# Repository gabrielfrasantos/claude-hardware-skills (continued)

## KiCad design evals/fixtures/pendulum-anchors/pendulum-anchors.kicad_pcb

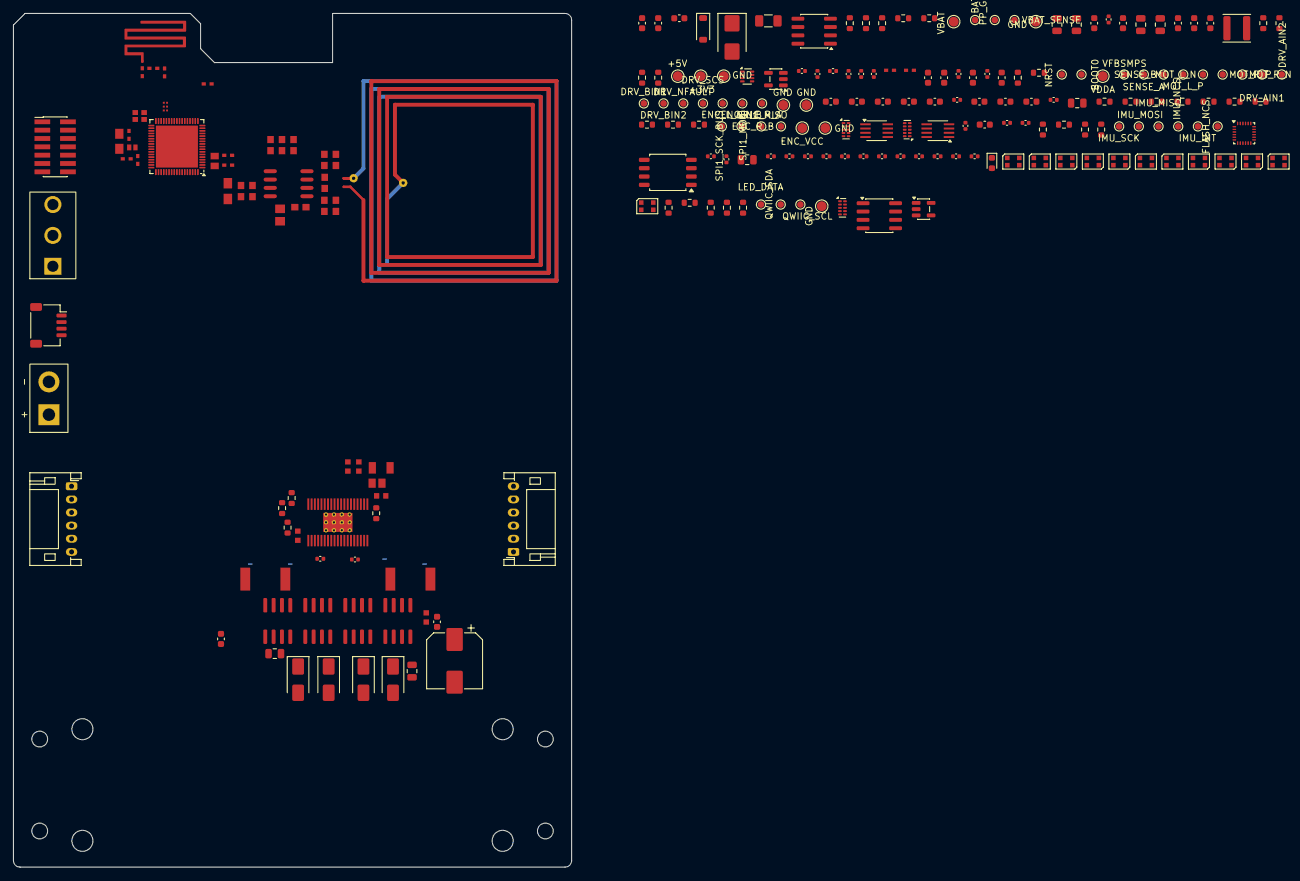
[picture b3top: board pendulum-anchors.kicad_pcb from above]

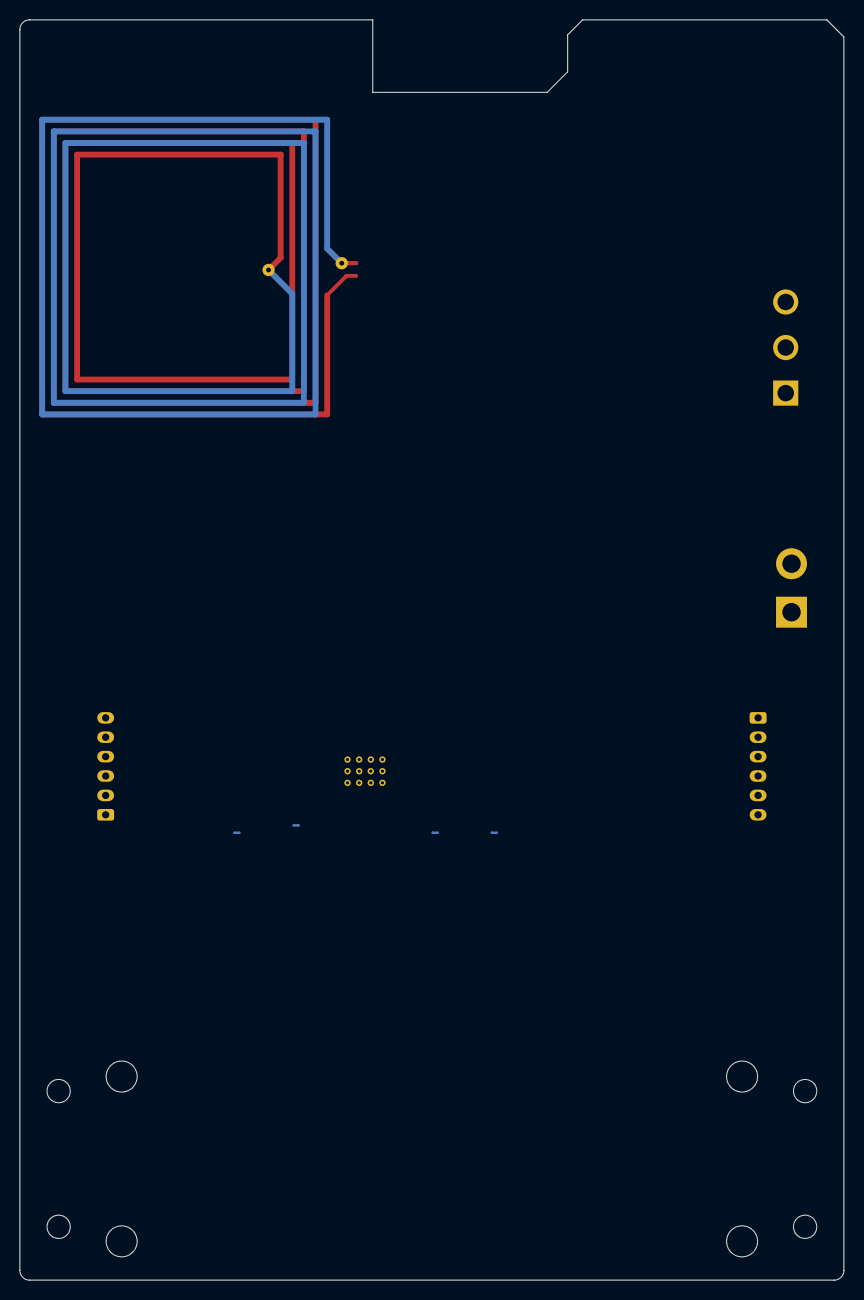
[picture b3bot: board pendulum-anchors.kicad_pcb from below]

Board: 4 copper layers, 85.0 x 130.0 mm, 245 parts (4 on the bottom side), 119 nets, no tracks yet.

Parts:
AE401: Meander antenna; MB1355_Meander_Antenna
AE801: ANT14; MB1163_ANT14
C101, C205: 47nF 50V; C_0603_1608Metric
C102, C209, C311, C313: 1uF 50V; C_0603_1608Metric
C103, C203, C208, C503, C506, C602, C603, C607: 100nF 50V; C_0603_1608Metric
C201, C202, C502, C505, C805: 10uF 25V; C_0805_2012Metric
C204, C301, C302, C303, C304, C305, C312, C317, C606, C610, C701, C703, C704, C801, C802, C806, C807, C808, C809, C810, C811, C812, C813, C814, C815, C816, C817: 100nF 16V; C_0402_1005Metric
C206, C207: 22uF 25V; C_0805_2012Metric
C210: 2.2uF 25V; C_0603_1608Metric
C306: 4.7uF 10V; C_0402_1005Metric
C307, C318: 100nF 16V; MB1355_0402_CAP_NPOL
C308: 100pF 50V; MB1355_0402_CAP_NPOL
C309, C314: 4.7uF 10V; MB1355_0402_CAP_NPOL
C310, C702: 10nF 50V; C_0603_1608Metric
C315, C316: 6.8pF 50V; MB1355_0402_CAP_NPOL
C401: NF; MB1355_0402_CAP_NPOL
C402: 1.2pF 50V; MB1355_0402_CAP_NPOL
C501, C504: 1nF 50V; C_0402_1005Metric
C507: 220u 35V; CP_Elec_8x10
C508: 10nF 100V; BOOST_0603L
C509: 1uF 50V; BOOST_0805L
C510: 100nF 100V; BOOST_0603L
C511: 100nF 25V; BOOST_0603L
C512: 1uF 16V; BOOST_0603L
C513: 1nF 16V; BOOST_0603L
C514: 1uF 100V; BOOST_1206L
C601: 10uF 10V; C_0603_1608Metric
C604, C605, C608, C609: 1nF 50V; C_0603_1608Metric
C803: 1uF 16V; MB1163_CP_293D_A
C804: 100nF 50V; MB1163_C_0603
C818: 100pF 50V; MB1163_C_0603
C819, C820: 47pF 50V; MB1163_C_0603
C821, C822, C823: NF; MB1163_C_0603
D101: BZT52C15; D_SOD-123
D102: SMBJ15A; D_SMB
D501, D502, D503, D504: SS34; D_SMA
D801: green; LED_0603_1608Metric
D802, D803, D804, D805, D806, D807, D808, D809, D810, D811, D812, D813: WS2812B-2020; LED_WS2812B-2020_PLCC4_2.0x2.0mm
F101: 4A fast; Fuse_1206_3216Metric
F601: PTC 100mA; Fuse_0805_2012Metric
FB301: BLM18PG221SN1D; L_0603_1608Metric
FB801: 742792042; MB1163_L_0805
FL401: MLPF-WB55-01E3; MB1355_ST_CSP650x58P2x3_160x100x42
J101: XT30 battery; AMASS_XT30UPB-F_1x02_P5.00mm_Vertical
J301: STDC14; PinHeader_2x07_P1.27mm_Vertical_SMD
J601: Motor left; JST_PH_S6B-PH-K_1x06_P2.00mm_Horizontal
J602: Motor right; JST_PH_S6B-PH-K_1x06_P2.00mm_Horizontal
J801: Qwiic; JST_SH_SM04B-SRSS-TB_1x04-1MP_P1.00mm_Horizontal
L201: 4.7uH; L_Sunlord_SWPA4030S
L301: 10uH; MB1355_0805_COIL
L302: 10nH; MB1355_IND_0402_MURATA_LQW15AN_H0P5
L401: 3.6nH; MB1355_0402_COIL
MB1, MB2, MB3, MB4: bracket M3; MountingHole_M3_NPTH_KeepOut7mm
MB5, MB6, MB7, MB8: bracket M2; MountingHole_M2_NPTH_KeepOut5.5mm
MC1, MC2, MC3, MC4: battery cradle; MountingHole_M3_NPTH_KeepOut7mm
MH1: bumper; MountingHole_M3_NPTH_KeepOut7mm
MH2: bumper (nylon); MountingHole_M3_NPTH_KeepOut7mm
NT501, NT502, NT503, NT504: NetTie; BOOST_Net-Tie_10mil
Q101: AO4805; SOIC-8_3.9x4.9mm_P1.27mm
Q501, Q502, Q503, Q504: CSD88537ND; BOOST_SO-8
R101, R102, R104: 100k; R_0603_1608Metric
R103: 1k; R_0603_1608Metric
R105: 27k; R_0603_1608Metric
R201: 240k; R_0603_1608Metric
R202: 36k; R_0603_1608Metric
R203: 52.3k; R_0603_1608Metric
R204, R302, R515, R516, R518, R701, R702, R703, R704, R803: 10k; R_0603_1608Metric
R301, R802: 33; R_0603_1608Metric
R401: 0; MB1355_0402_RES
R509, R512: 50m; BOOST_2512M
R517, R603, R605, R607, R609, R808, R809: 2.2k; R_0603_1608Metric
R601, R602: 0; R_0603_1608Metric
R604, R606, R608, R610: 100; R_0603_1608Metric
R801: 470; R_0603_1608Metric
R804: 30k; MB1163_R_0603
R805, R806: 4.7k; MB1163_R_0603
R810: 20k; MB1163_R_0603
SW101: SS-12D10L5; SW_Slide_SPDT_SS-12D10L5_P4.70mm
TP101: VBAT; TestPoint_Pad_D1.5mm
TP102: BAT_F; TestPoint_Pad_D1.0mm
TP103: PP_G; TestPoint_Pad_D1.0mm
TP104: VBAT_SENSE; TestPoint_Pad_D1.0mm
TP105, TP203, TP516, TP517, TP606, TP804: GND; TestPoint_Pad_D1.5mm
TP201: +5V; TestPoint_Pad_D1.5mm
TP202: +3V3; TestPoint_Pad_D1.5mm
TP301: NRST; TestPoint_Pad_D1.0mm
TP302: BOOT0; TestPoint_Pad_D1.0mm
TP303: VDDA; TestPoint_Pad_D1.5mm
TP304: VFBSMPS; TestPoint_Pad_D1.0mm
TP501: SENSE_A; TestPoint_Pad_D1.0mm
TP502: SENSE_B; TestPoint_Pad_D1.0mm
TP503: MOT_L_P; TestPoint_Pad_D1.0mm
TP504: MOT_L_N; TestPoint_Pad_D1.0mm
TP505: MOT_R_P; TestPoint_Pad_D1.0mm
TP506: MOT_R_N; TestPoint_Pad_D1.0mm
TP507: DRV_AIN1; TestPoint_Pad_D1.0mm
TP508: DRV_AIN2; TestPoint_Pad_D1.0mm
TP509: DRV_BIN1; TestPoint_Pad_D1.0mm
TP510: DRV_BIN2; TestPoint_Pad_D1.0mm
TP511: DRV_NFAULT; TestPoint_Pad_D1.0mm
TP512: DRV_SCS; TestPoint_Pad_D1.0mm
TP513: SPI1_SCK_BUS; TestPoint_Pad_D1.0mm
TP514: SPI1_MOSI; TestPoint_Pad_D1.0mm
TP515: SPI1_MISO; TestPoint_Pad_D1.0mm
TP601: ENC_L_A; TestPoint_Pad_D1.0mm
TP602: ENC_L_B; TestPoint_Pad_D1.0mm
TP603: ENC_R_A; TestPoint_Pad_D1.0mm
TP604: ENC_R_B; TestPoint_Pad_D1.0mm
TP605: ENC_VCC; TestPoint_Pad_D1.5mm
TP701: IMU_SCK; TestPoint_Pad_D1.0mm
TP702: IMU_MOSI; TestPoint_Pad_D1.0mm
TP703: IMU_MISO; TestPoint_Pad_D1.0mm
TP704: IMU_NCS; TestPoint_Pad_D1.0mm
TP705: IMU_INT; TestPoint_Pad_D1.0mm
TP706: FLASH_NCS; TestPoint_Pad_D1.0mm
TP801: LED_DATA; TestPoint_Pad_D1.0mm
TP802: QWIIC_SDA; TestPoint_Pad_D1.0mm
TP803: QWIIC_SCL; TestPoint_Pad_D1.0mm
U201: TPS62933F; SOT-583-8
U202: TLV75533P; SOT-23-5
U301: STM32WB55RGV6; QFN-68-1EP_8x8mm_P0.4mm_EP6.4x6.4mm
U501: DRV8711; BOOST_R-PDSO-G38
U601, U603, U801: TPD4E05U06QDQARQ1; USON-10_2.5x1.0mm_P0.5mm
U602, U604: SN74LVC3G17DCTR; SSOP-8_2.95x2.8mm_P0.65mm
U701: MPU-6500; InvenSense_QFN-24_3x3mm_P0.4mm
U702: W25Q16JVSSIQ; SOIC-8_5.3x5.3mm_P1.27mm
U802: M24C64-RMN6TP; SOIC-8_3.9x4.9mm_P1.27mm
U803: M24SR64-YMN6T/2; MB1163_SO8
U804: SN74AHCT1G125; SOT-23-5
Y301: 32MHz; MB1355_NX2016_4P
Y302: 32.768kHz; MB1355_NX2012_2P

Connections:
+3V3: C210.1, C301.1, C302.1, C303.1, C304.1, C305.1, C306.1, C307.1, C308.1, C309.1, C318.1, C606.1, C610.1, C701.1, C702.1, C704.1, C802.1, FB301.1, FB801.1, J301.3, J801.2, R515.2, R516.2, R517.2, R602.1, R701.2, R702.2, R703.2, R704.2, R805.2, R806.2, R808.2, R809.2, R810.2, TP202.1, U202.5, U301.1, U301.30, U301.33, U301.44, U301.45, U301.55, U301.68, U602.8, U604.8, U701.8, U701.13, U702.8, U801.4, U802.8
+5V: C206.1, C207.1, C208.1, C209.1, C801.1, C805.1, C806.1, C807.1, C808.1, C809.1, C810.1, C811.1, C812.1, C813.1, C814.1, C815.1, C816.1, C817.1, D802.4, D803.4, D804.4, D805.4, D806.4, D807.4, D808.4, D809.4, D810.4, D811.4, D812.4, D813.4, L201.2, R203.1, R601.1, TP201.1, U202.1, U202.3, U804.5
/1 Battery input and protection/BAT_F: F101.2, Q101.7, Q101.8, TP102.1
/1 Battery input and protection/BAT_P: F101.1, J101.1
/1 Battery input and protection/PP_G: C102.1, D101.2, Q101.2, Q101.4, R101.1, R102.1, R103.1, TP103.1
/1 Battery input and protection/PP_S: C102.2, D101.1, Q101.1, Q101.3, R101.2
/1 Battery input and protection/PP_SS: C101.1, R103.2
/1 Battery input and protection/SW_ON: R102.2, SW101.2
/2 5V0 buck and 3V3 LDO/BUCK_BST: C204.1, U201.6
/2 5V0 buck and 3V3 LDO/BUCK_EN: R201.2, R202.1, U201.2
/2 5V0 buck and 3V3 LDO/BUCK_FB: R203.2, R204.1, U201.8
/2 5V0 buck and 3V3 LDO/BUCK_SS: C205.1, U201.7
/2 5V0 buck and 3V3 LDO/BUCK_SW: C204.2, L201.1, U201.5
/3 MCU, clocks, supplies, debug/BOOT0: R302.1, TP302.1, U301.5
/3 MCU, clocks, supplies, debug/HSE_IN: U301.35, Y301.1
/3 MCU, clocks, supplies, debug/HSE_OUT: U301.34, Y301.3
/3 MCU, clocks, supplies, debug/NRST: C317.1, J301.12, TP301.1, U301.8
/3 MCU, clocks, supplies, debug/OSC32_IN: C315.1, U301.3, Y302.1
/3 MCU, clocks, supplies, debug/OSC32_OUT: C316.1, U301.4, Y302.2
/3 MCU, clocks, supplies, debug/SMPS_LX: L302.1, U301.43
/3 MCU, clocks, supplies, debug/SMPS_MID: L301.1, L302.2
/3 MCU, clocks, supplies, debug/SPI1_SCK: R301.1, U301.63
/3 MCU, clocks, supplies, debug/SWCLK: J301.6, U301.56
/3 MCU, clocks, supplies, debug/SWDIO: J301.4, U301.54
/3 MCU, clocks, supplies, debug/VCP_RX: J301.13, U301.67
/3 MCU, clocks, supplies, debug/VCP_TX: J301.14, U301.66
/3 MCU, clocks, supplies, debug/VFBSMPS: C314.1, L301.2, TP304.1, U301.41
/4 2.4 GHz RF path and antenna/RF_50: FL401.A1, R401.1
/4 2.4 GHz RF path and antenna/RF_ANT: AE401.1, C402.1, L401.2
/4 2.4 GHz RF path and antenna/RF_MATCH: C401.1, L401.1, R401.2
/5 Motor drive (DRV8711 + external FETs)/A1HS: Q501.2, U501.36
/5 Motor drive (DRV8711 + external FETs)/A1LS: Q501.4, U501.35
/5 Motor drive (DRV8711 + external FETs)/A2HS: Q502.4, U501.31
/5 Motor drive (DRV8711 + external FETs)/A2LS: Q502.2, U501.32
/5 Motor drive (DRV8711 + external FETs)/B1HS: Q503.2, U501.27
/5 Motor drive (DRV8711 + external FETs)/B1LS: Q503.4, U501.26
/5 Motor drive (DRV8711 + external FETs)/B2HS: Q504.4, U501.22
/5 Motor drive (DRV8711 + external FETs)/B2LS: Q504.2, U501.23
/5 Motor drive (DRV8711 + external FETs)/DRV_AISENN: C501.2, NT503.1, U501.33
/5 Motor drive (DRV8711 + external FETs)/DRV_AISENP: C501.1, NT501.1, U501.34
/5 Motor drive (DRV8711 + external FETs)/DRV_BEMF: C513.1, U501.20
/5 Motor drive (DRV8711 + external FETs)/DRV_BISENN: C504.2, NT504.1, U501.24
/5 Motor drive (DRV8711 + external FETs)/DRV_BISENP: C504.1, NT502.1, U501.25
/5 Motor drive (DRV8711 + external FETs)/DRV_CP1: C510.1, U501.1
/5 Motor drive (DRV8711 + external FETs)/DRV_CP2: C510.2, U501.2
/5 Motor drive (DRV8711 + external FETs)/DRV_V5: C511.1, U501.6
/5 Motor drive (DRV8711 + external FETs)/DRV_VCP: C509.1, U501.3
/5 Motor drive (DRV8711 + external FETs)/DRV_VINT: C512.1, U501.7
/5 Motor drive (DRV8711 + external FETs)/SENSE_A: NT501.2, Q501.3, Q502.1, R509.1, TP501.1
/5 Motor drive (DRV8711 + external FETs)/SENSE_B: NT502.2, Q503.3, Q504.1, R512.1, TP502.1
/6 Motor connectors and encoder inputs/ENC_L_A_F: C604.1, R604.2, U602.1
/6 Motor connectors and encoder inputs/ENC_L_A_RAW: J601.3, R603.1, R604.1, U601.1
/6 Motor connectors and encoder inputs/ENC_L_B_F: C605.1, R606.2, U602.6
/6 Motor connectors and encoder inputs/ENC_L_B_RAW: J601.4, R605.1, R606.1, U601.2
/6 Motor connectors and encoder inputs/ENC_R_A_F: C608.1, R608.2, U604.1
/6 Motor connectors and encoder inputs/ENC_R_A_RAW: J602.3, R607.1, R608.1, U603.1
/6 Motor connectors and encoder inputs/ENC_R_B_F: C609.1, R610.2, U604.6
/6 Motor connectors and encoder inputs/ENC_R_B_RAW: J602.4, R609.1, R610.1, U603.2
/6 Motor connectors and encoder inputs/ENC_SRC: F601.1, R601.2, R602.2
/6 Motor connectors and encoder inputs/ENC_VCC: C601.1, C602.1, F601.2, J601.2, J602.2, R603.2, R605.2, R607.2, R609.2, TP605.1, U601.5, U603.5
/7 IMU and SPI flash/FLASH_HOLD: R704.1, U702.7
/7 IMU and SPI flash/FLASH_WP: R703.1, U702.3
/7 IMU and SPI flash/IMU_REGOUT: C703.1, U701.10
/8 User interface, expansion, test points/LED_BUF: R802.1, U804.4
/8 User interface, expansion, test points/LED_D1: D802.3, R802.2
/8 User interface, expansion, test points/LED_D2: D802.1, D803.3
/8 User interface, expansion, test points/LED_D3: D803.1, D804.3
/8 User interface, expansion, test points/LED_D4: D804.1, D805.3
/8 User interface, expansion, test points/LED_D5: D805.1, D806.3
/8 User interface, expansion, test points/LED_D6: D806.1, D807.3
/8 User interface, expansion, test points/LED_D7: D807.1, D808.3
/8 User interface, expansion, test points/LED_D8: D808.1, D809.3
/8 User interface, expansion, test points/LED_D9: D809.1, D810.3
/8 User interface, expansion, test points/LED_D10: D810.1, D811.3
/8 User interface, expansion, test points/LED_D11: D811.1, D812.3
/8 User interface, expansion, test points/LED_D12: D812.1, D813.3
/8 User interface, expansion, test points/LED_G_A: D801.2, R801.2
/8 User interface, expansion, test points/NFC_AC0: AE801.1, C820.1, C822.1, C823.1, U803.2
/8 User interface, expansion, test points/NFC_AC1: AE801.2, C819.1, C821.1, C823.2, U803.3
/8 User interface, expansion, test points/NFC_VCC: C803.1, C804.1, C818.1, FB801.2, U803.8
DRV_AIN1: TP507.1, U301.51, U501.10
DRV_AIN2: TP508.1, U301.52, U501.11
DRV_BIN1: TP509.1, U301.23, U501.12
DRV_BIN2: TP510.1, U301.24, U501.13
DRV_NFAULT: R515.1, TP511.1, U301.21, U301.25, U501.18
DRV_NSLEEP: R518.1, U301.6, U501.8
DRV_NSTALL: R516.1, U301.27, U501.19
DRV_RESET: U301.7, U501.9
DRV_SCS: TP512.1, U301.19, U501.16
ENC_L_A: TP601.1, U301.9, U602.7
ENC_L_B: TP602.1, U301.11, U602.2
ENC_L_Z: U301.26, U602.5
ENC_R_A: TP603.1, U301.15, U604.7
ENC_R_B: TP604.1, U301.16, U604.2
ENC_R_Z: U301.12, U604.5
FLASH_NCS: R702.1, TP706.1, U301.57, U702.1
GND: C103.2, C201.2, C202.2, C203.2, C205.2, C206.2, C207.2, C208.2, C209.2, C210.2, C301.2, C302.2, C303.2, C304.2, C305.2, C306.2, C307.2, C308.2, C309.2, C310.2, C311.2, C312.2, C313.2, C314.2, C315.2, C316.2, C317.2, C318.2, C401.2, C402.2, C502.2, C503.2, C505.2, C506.2, C507.2, C508.2, C511.2, C512.2, C513.2, C514.2, C601.2, C602.2, C604.2, C605.2, C606.2, C608.2, C609.2, C610.2, C701.2, C702.2, C703.2, C704.2, C801.2, C802.2, C803.2, C804.2, C805.2, C806.2, C807.2, C808.2, C809.2, C810.2, C811.2, C812.2, C813.2, C814.2, C815.2, C816.2, C817.2, C818.2, C819.2, C820.2, C821.2, C822.2, D102.2, D501.2, D502.2, D503.2, D504.2, D801.1, D802.2, D803.2, D804.2, D805.2, D806.2, D807.2, D808.2, D809.2, D810.2, D811.2, D812.2, D813.2, FL401.A2, FL401.B1, FL401.B2, FL401.B3, J101.2, J301.5, J301.7, J301.11, J601.5, J602.5, J801.1, J801.MP, NT503.2, NT504.2, R105.2, R202.2, R204.2, R302.2, R509.2, R512.2, R518.2, R803.2, R804.2, SW101.1, TP105.1, TP203.1, TP516.1, TP517.1, TP606.1, TP804.1, U201.1, U201.4, U202.2, U301.32, U301.42, U301.69, U501.5, U501.29, U501.38, U501.39, U601.3, U601.8, U602.3, U602.4, U603.3, U603.8, U604.3, U604.4, U701.11, U701.18, U701.20, U702.4, U801.3, U801.8, U802.1, U802.2, U802.3, U802.4, U802.7, U803.4, U804.1, U804.3, Y301.2, Y301.4
IMU_INT: TP705.1, U301.50, U701.12
IMU_MISO: TP703.1, U301.48, U701.9
IMU_MOSI: TP702.1, U301.49, U701.24
IMU_NCS: R701.1, TP704.1, U301.46, U701.22
IMU_SCK: TP701.1, U301.47, U701.23
LED_DATA: R803.1, TP801.1, U301.22, U804.2
LED_GREEN: R801.1, U301.38
MOT_L_N: C603.2, D504.1, J601.1, Q504.3, Q504.7, Q504.8, TP504.1, U501.21
MOT_L_P: C603.1, D503.1, J601.6, Q503.1, Q503.5, Q503.6, TP503.1, U501.28
MOT_R_N: C607.2, D502.1, J602.1, Q502.3, Q502.7, Q502.8, TP506.1, U501.30
MOT_R_P: C607.1, D501.1, J602.6, Q501.1, Q501.5, Q501.6, TP505.1, U501.37
NFC_GPO: R810.1, U301.17, U803.7
NFC_RF_DIS: R804.1, U301.18, U803.1
QWIIC_SCL: J801.4, R806.1, R809.1, TP803.1, U301.28, U801.2, U802.6, U803.6
QWIIC_SDA: J801.3, R805.1, R808.1, TP802.1, U301.29, U801.1, U802.5, U803.5
RF1: FL401.A3, U301.31
SPI1_MISO: R517.1, TP515.1, U301.64, U501.17, U702.2
SPI1_MOSI: TP514.1, U301.65, U501.15, U702.5
SPI1_SCK_BUS: R301.2, TP513.1, U501.14, U702.6
VBAT: C101.2, C201.1, C202.1, C203.1, C502.1, C503.1, C505.1, C506.1, C507.1, C508.1, C509.2, C514.1, D102.1, Q101.5, Q101.6, Q501.7, Q501.8, Q502.5, Q502.6, Q503.7, Q503.8, Q504.5, Q504.6, R104.1, R201.1, TP101.1, U201.3, U501.4
VBAT_SENSE: C103.1, R104.2, R105.1, TP104.1, U301.10
VDDA: C310.1, C311.1, C312.1, C313.1, FB301.2, TP303.1, U301.13, U301.14
